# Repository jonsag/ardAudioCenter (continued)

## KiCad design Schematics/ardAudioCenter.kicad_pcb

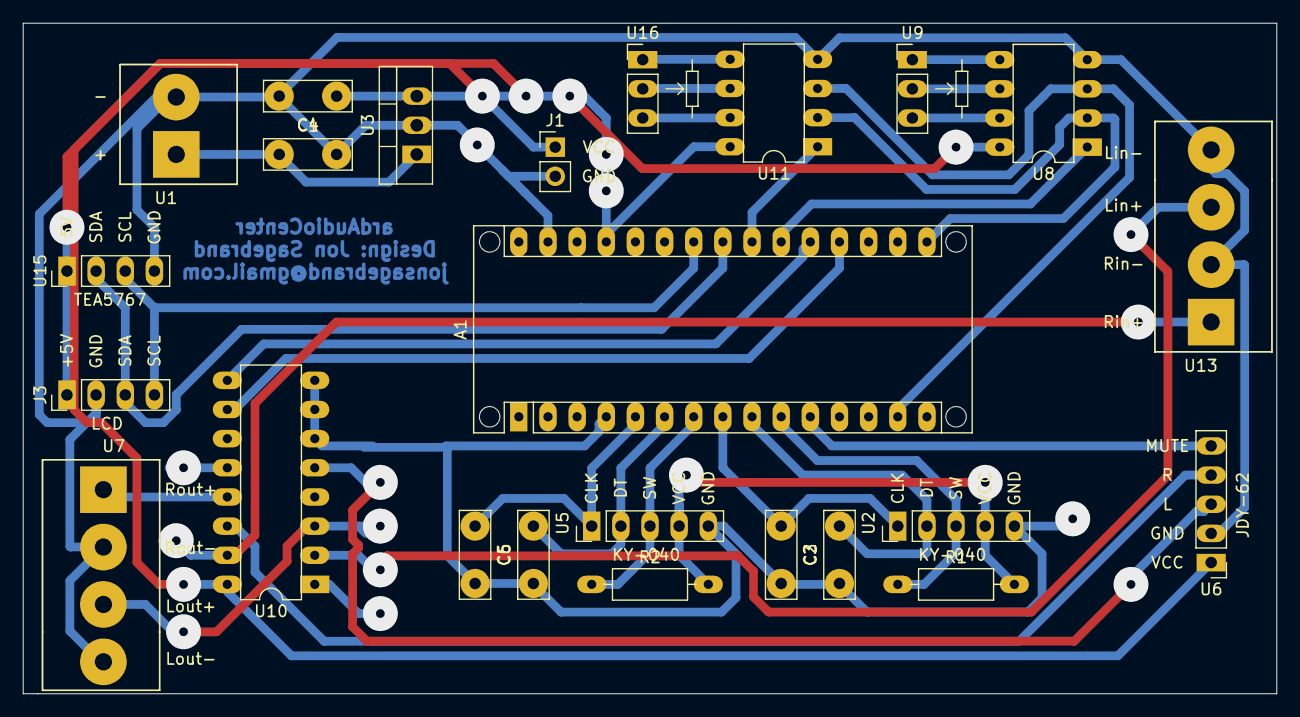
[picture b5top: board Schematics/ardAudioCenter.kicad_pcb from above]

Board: 2 copper layers, 109.2 x 58.4 mm, 24 parts (0 on the bottom side), 30 nets.

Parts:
A1: Arduino_Nano_v3.x; Arduino_Nano_WithMountingHoles_larger
C1: 0.33u; C_Disc_D7.5mm_W2.5mm_P5.00mm_larger
C2, C3, C5, C6: 0.47u; C_Disc_D7.5mm_W2.5mm_P5.00mm_larger
C4: 0.1u; C_Disc_D7.5mm_W2.5mm_P5.00mm_larger
J1: 2-pin_power_input_header
J3: 4-pin_I2C_LCD_header; 4-pin_I2C_LCD_header_larger
R1, R2: 10k; R_Axial_DIN0207_L6.3mm_D2.5mm_P10.16mm_Horizontal_larger_pa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
U1: 2-pole_power_in_screw_terminal
U2, U5: KY-040_Rotary_Encoder; 5-pin_KY-040_rotary_encoder_header_larger
U3: L7805; TO-220-3_Vertical_larger
U6: JDY-62_Bluetooth_Module; 5-pin_JDY-62_bluetooth_module_header_large
U7: 4-pole_RL-output_screw_terminal; 4-pole_screw_terminal_RL_output
U8, U11: MCP41010; DIP-8_W7.62mm_large
U9, U16: 3-pin_potentiometer_output; 3-pin_potentiometer_header_larger_pads
U10: CD4052B; DIP-16_W7.62mm_larger
U13: 4-pole_RL-input_screw_terminal; 4-pole_screw_terminal_RL_input
U15: TEA5767_FM_Radio_Module; 4-pin_TEA5767_radio_module_header_large

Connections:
+5V: A1.27 (+5V), C4.1, J1.1 (VCC), J3.1 (+5V), R1.2, R2.2, U2.4 (VCC), U3.3 (OUT), U5.4 (VCC), U6.1 (VCC), U8.8 (VDD), U10.16 (VDD), U11.8 (VDD), U15.1 (5V)
+12V: C1.1, U1.1 (+), U3.1 (IN)
/Lout+: U7.3 (Lout+), U10.3 (Y)
/Rout+: U7.1 (Rout+), U10.13 (X)
BTL+: U6.3 (L), U10.5 (Y1)
BTR+: U6.4 (R), U10.14 (X1)
GND: A1.4 (GND), A1.29 (GND), C1.2, C2.2, C3.1, C4.2, C5.2, C6.1, J1.2 (GND), J3.3 (GND), U1.2 (-), U2.5 (GND), U3.2 (GND), U5.5 (GND), U6.2 (GND), U7.2 (Rout-), U7.4 (Lout-), U8.4 (VSS), U10.6 (INH), U10.7 (VEE), U10.8 (VSS), U11.4 (VSS), U13.2 (Rin-), U13.4 (Lin-), U15.4 (GND)
LineL+: U10.2 (Y2), U13.3 (Lin+)
LineR+: U10.15 (X2), U13.1 (Rin+)
unnamed: A1.5 (D2), C5.1, U5.1 (CLK)
unnamed: A1.6 (D3), C6.2, U5.2 (DT)
unnamed: A1.7 (D4), R2.1, U5.3 (SW)
unnamed: A1.8 (D5), C2.1, U2.1 (CLK)
unnamed: A1.9 (D6), C3.2, U2.2 (DT)
unnamed: A1.10 (D7), R1.1, U2.3 (SW)
unnamed: A1.11 (D8), U6.5 (MUTE)
unnamed: A1.14 (D11), U8.3 (SI), U11.3 (SI)
unnamed: A1.16 (D13), U8.2 (SCK), U11.2 (SCK)
unnamed: A1.19 (A0), U10.10 (A)
unnamed: A1.20 (A1), U10.9 (B)
unnamed: A1.21 (A2), U8.1 (~CS)
unnamed: A1.22 (A3), U11.1 (~CS)
unnamed: A1.23 (A4), J3.5 (SDA), U15.2 (SDA)
unnamed: A1.24 (A5), J3.7 (SCL), U15.3 (SCL)
unnamed: U8.5 (PA0), U9.1 (PAO)
unnamed: U8.6 (PW0), U9.2 (PW0)
unnamed: U8.7 (PB0), U9.3 (PB0)
unnamed: U11.5 (PA0), U16.1 (PAO)
unnamed: U11.6 (PW0), U16.2 (PW0)
unnamed: U11.7 (PB0), U16.3 (PB0)

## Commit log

2020-05-26 first layout of schematics
2020-05-26 first sketch
2020-05-27 schematics
2020-05-27 sketch now changes function
2020-05-27 encoder is read
2020-05-27 volume up/down
2020-05-28 now selects source
2020-05-30 switched to arduino nano, now sets source and mux
2020-05-30 now writes to potentiometers and sets balance
2020-05-30 added volume bar
2020-05-30 added radio and sd card modules
2020-05-31 added bluetooth module
2020-05-31 went back to arduino nano and added second encoder again
2020-05-31 giving nodemcu another go
2020-05-31 nah, no nodemcu
2020-06-02 second rotary controls radio
2020-06-03 pcb routing
2020-06-04 experimented with radio
2020-06-04 pcb v1
2020-06-05 PCB v1.1
2020-06-10 sketch
2020-06-10 changed bt hookup
2022-03-20 new pcb
2022-05-13 deleted kicad5
2022-05-15 pcb, moved to pio
2022-05-16 2-layer PCB
2022-05-19 kicad
2022-05-20 cleaned up code
2022-05-20 minor changes
2022-05-20 got the old arduino code back
2022-05-20 cleaning
2022-05-21 added SPI as lib_dep
2022-05-21 added brackets, (), after SPI.begin
2022-05-21 correcting output on source select
2022-05-21 DFPlayer work
2022-05-22 now debug and info, more work on dfplayer
2022-05-22 more DFPlayer work
2022-05-22 new 3D
2022-05-23 possible to deselect DFPlayer
2022-05-25 amplifiers
2022-05-25 deleted old arduino ino files
2022-05-26 Dual amplifier
2022-05-31 PCBs
2022-06-12 volume and steps
2022-06-12 deleted schematics
2022-06-12 vscode settings
2022-06-23 new volumes
2022-08-14 bluetooth controlled with MOSFET
2022-08-14 readme
2022-08-15 typo
2022-09-01 atmega pcb
2023-02-21 kicad7
